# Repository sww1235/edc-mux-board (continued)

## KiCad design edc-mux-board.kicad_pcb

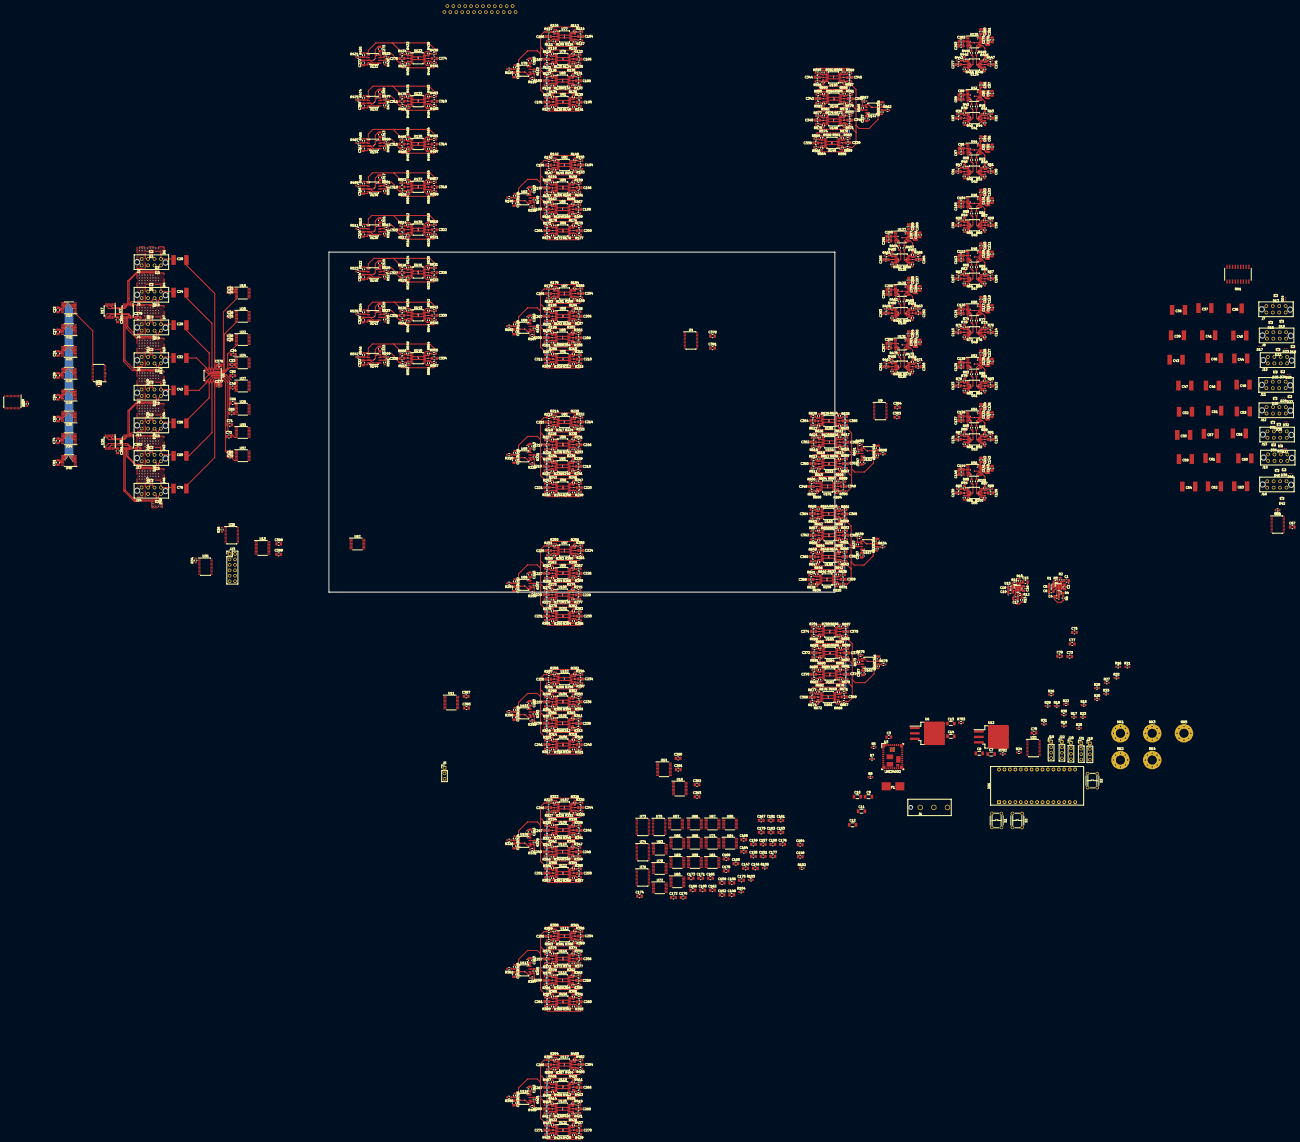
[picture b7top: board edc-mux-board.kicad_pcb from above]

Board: 4 copper layers, 1341 parts (1 on the bottom side), 1027 nets.

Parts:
C1, C4, C15, C17: 2u2F; C_0805_2012Metric_Pad1.15x1.50mm_HandSolder
C2, C16: 0.47uF; C_0805_2012Metric_Pad1.15x1.50mm_HandSolder
C3: 15uF; C_0805_2012Metric_Pad1.15x1.50mm_HandSolder
C5, C6, C18, C19: 4u7F; C_0805_2012Metric_Pad1.15x1.50mm_HandSolder
C7, C8, C13, C14: 10uF; C_1206_3216Metric_Pad1.24x1.80mm_HandSolder
C9, C10, C11, C12: 22uF; C_1206_3216Metric_Pad1.24x1.80mm_HandSolder
C20, C24, C28, C32, C35, C36, C37, C39, C40, C41, C42, C43, C44, C45, C46, C47, C48, C51, C52, C53, C55, C56, C57, C58, C59, C60, C61, C62, C63, C64, C69, C76: 1uF; Kemet_CAP_2220_5750Metric
C21, C22, C23, C25, C26, C27, C29, C30, C31, C33, C34, C38, C49, C50, C54, C65, C66, C67, C68, C70, C71, C72, C73, C74, C75, C77, C78, C79, C80, C81, C82, C83, C85, C86, C89, C90, C91, C93, C94, C97, C98, C99, C101, C102, C105, C106, C107, C109, C110, C113, C114, C115, C117, C118, C121, C122, C123, C125, C126, C129, C130, C131, C133, C134, C137, C138, C139, C141, C142, C145, C146, C147, C148, C149, C150, C151, C152, C153, C154, C155, C156, C157, C158, C159, C160, C161, C162, C163, C164, C165, C166, C167, C168, C169, C170, C171, C172, C173, C174, C175, C176, C177, C178, C179, C180, C181, C182, C183, C184, C185, C186, C187, C188, C189, C190, C191, C192, C193, C194, C195, C196, C197, C198, C199, C200, C201, C202, C203, C204, C205, C206, C207, C208, C209, C210, C211, C212, C213, C214, C215, C216, C217, C218, C219, C220, C221, C222, C223, C224, C225, C226, C227, C228, C229, C230, C231, C232, C233, C234, C235, C236, C237, C238, C239, C240, C241, C242, C243, C244, C245, C246, C247, C248, C249, C250, C251, C252, C253, C254, C255, C256, C257, C258, C259, C260, C261, C262, C263, C264, C265, C266, C267, C268, C269, C270, C271, C272, C273, C274, C275, C276, C277, C279, C280, C283, C284, C285, C287, C288, C291, C292, C293, C295, C296, C299, C300, C301, C303, C304, C307, C308, C309, C310, C311, C312, C313, C314, C315, C316, C317, C318, C319, C320, C321, C322, C323, C324, C325, C326, C327, C328, C329, C330, C331, C332, C333, C334, C335, C336, C337, C338, C339, C340, C341, C342, C343, C344, C345, C346, C347, C348, C349, C350, C351, C352, C353, C354, C355, C356, C357, C358, C359, C360, C361, C362, C363, C364, C365, C366, C367, C368, C369, C370, C371, C372, C373, C374, C375, C376, C377, C378, C379, C380, C381, C382, C383, C384, C385, C386, C387, C388, C389, C390, C391, C392, C393: 0.1uF; C_0805_2012Metric_Pad1.15x1.50mm_HandSolder
C84, C87, C88, C92, C95, C96, C100, C103, C104, C108, C111, C112, C116, C119, C120, C124, C127, C128, C132, C135, C136, C140, C143, C144, C278, C281, C282, C286, C289, C290, C294, C297, C298, C302, C305, C306: 0.01uF; C_0805_2012Metric_Pad1.15x1.50mm_HandSolder
D1, D4, D7, D10, D14, D17, D19, D23, D26, D29, D32, D34, D37, D41, D43, D46: TPD1E10B06; DPY_(R-PX1SON-N2)
D2, D3, D5, D6, D8, D9, D11, D12, D13, D15, D16, D18, D20, D21, D22, D24, D25, D27, D28, D30, D31, D33, D35, D36, D38, D39, D40, D42, D44, D45, D47, D48: 0582BQ; SC-75_3L
F1: 5A; NANO-0154-OMNI-BLOK-Fuse-Holder
J1: Power In; 43255-0121
J2: Device 0; 3-794681-8
J3: Device 1; 3-794681-8
J4: Device 2; 3-794681-8
J5: Mixer Audio In; PinHeader_1x03_P2.54mm_Vertical
J6: Device 3; 3-794681-8
J7: Headset 0; 3-794681-8
J8: Headset 1; 3-794681-8
J9: Device 4; 3-794681-8
J10: Headset 2; 3-794681-8
J11: Headset 3; 3-794681-8
J12: Headset 4; 3-794681-8
J13: Headset 5; 3-794681-8
J14: Device 5; 3-794681-8
J15: Headset 6; 3-794681-8
J16: Headset 7; 3-794681-8
J17: Device 6; 3-794681-8
J18: 5V-I2C-2; PinHeader_1x04_P2.54mm_Vertical
J19: 5V-I2C-3; PinHeader_1x04_P2.54mm_Vertical
J20: 5V-I2C-4; PinHeader_1x04_P2.54mm_Vertical
J21: 5V-I2C-5; PinHeader_1x04_P2.54mm_Vertical
J22: 5V-I2C-6; PinHeader_1x04_P2.54mm_Vertical
J23: Extra GPIO; PinHeader_2x06_P2.54mm_Vertical
J24: Device 7; 3-794681-8
J25: Outputs to Mixer; SDB-25PFFP-SR8001
MK1, MK2, MK3, MK4, MK5: Mounting_Hole_PAD; MountingHole_4.3mm_M4_Pad_Via
R2, R6: 75kΩ; R_0603_1608Metric_Pad0.84x1.00mm_HandSolder
R3, R4, R11, R12: 68kΩ; R_0603_1608Metric_Pad0.84x1.00mm_HandSolder
R5: 174kΩ; R_0603_1608Metric_Pad0.84x1.00mm_HandSolder
R7: 22.6kΩ; R_0603_1608Metric_Pad0.84x1.00mm_HandSolder
R8: 143kΩ; R_0603_1608Metric_Pad0.84x1.00mm_HandSolder
R10, R13: 220kΩ; R_0603_1608Metric_Pad0.84x1.00mm_HandSolder
R14, R24, R34, R35, R36, R37, R42, R45, R50, R53, R58, R61, R66, R69, R74, R77, R82, R85, R90, R93, R98, R101, R102, R103, R104, R105, R446, R449, R454, R457, R462, R465, R470, R473: 10kΩ; R_0603_1608Metric_Pad0.84x1.00mm_HandSolder
R15, R16, R17, R18, R19, R20, R21, R22, R23, R25, R26, R27, R28, R29, R30, R31, R32, R33: 4k7Ω; R_0603_1608Metric_Pad0.84x1.00mm_HandSolder
R38, R39, R40, R41, R43, R44, R46, R47, R48, R49, R51, R52, R54, R55, R56, R57, R59, R60, R62, R63, R64, R65, R67, R68, R70, R71, R72, R73, R75, R76, R78, R79, R80, R81, R83, R84, R86, R87, R88, R89, R91, R92, R94, R95, R96, R97, R99, R100, R106, R107, R108, R109, R110, R111, R112, R113, R114, R115, R116, R117, R118, R119, R120, R121, R122, R123, R124, R125, R126, R127, R128, R129, R130, R131, R132, R133, R134, R135, R136, R137, R138, R139, R140, R141, R142, R143, R144, R145, R146, R147, R148, R149, R150, R151, R152, R153, R154, R155, R156, R157, R158, R159, R160, R161, R162, R163, R164, R165, R166, R167, R168, R169, R170, R171, R172, R173, R174, R175, R176, R177, R178, R179, R180, R181, R182, R183, R184, R185, R186, R187, R188, R189, R190, R191, R192, R193, R194, R195, R196, R197, R198, R199, R200, R201, R202, R203, R204, R205, R206, R207, R208, R209, R210, R211, R212, R213, R214, R215, R216, R217, R218, R219, R220, R221, R222, R223, R224, R225, R226, R227, R228, R229, R230, R231, R232, R233, R234, R235, R236, R237, R238, R239, R240, R241, R242, R243, R244, R245, R246, R247, R248, R249, R250, R251, R252, R253, R254, R255, R256, R257, R258, R259, R260, R261, R262, R263, R264, R265, R266, R267, R268, R269, R270, R271, R272, R273, R274, R275, R276, R277, R278, R279, R280, R281, R282, R283, R284, R285, R286, R287, R288, R289, R290, R291, R292, R293, R294, R295, R296, R297, R298, R299, R300, R301, R302, R303, R304, R305, R306, R307, R308, R309, R310, R311, R312, R313, R314, R315, R316, R317, R318, R319, R320, R321, R322, R323, R324, R325, R326, R327, R328, R329, R330, R331, R332, R333, R334, R335, R336, R337, R338, R339, R340, R341, R342, R343, R344, R345, R346, R347, R348, R349, R350, R351, R352, R353, R354, R355, R356, R357, R358, R359, R360, R361, R362, R363, R364, R365, R366, R367, R368, R369, R370, R371, R372, R373, R374, R375, R376, R377, R378, R379, R380, R381, R382, R383, R384, R385, R386, R387, R388, R389, R390, R391, R392, R393, R394, R395, R396, R397, R398, R399, R400, R401, R402, R403, R404, R405, R406, R407, R408, R409, R410, R411, R412, R413, R414, R415, R416, R417, R418, R419, R420, R421, R422, R423, R424, R425, R426, R427, R428, R429, R430, R431, R432, R433, R434, R435, R436, R437, R438, R439, R440, R441, R442, R443, R444, R445, R447, R448, R450, R451, R452, R453, R455, R456, R458, R459, R460, R461, R463, R464, R466, R467, R468, R469, R471, R472, R474, R475, R476, R477, R478, R479, R480, R481, R482, R483, R484, R485, R486, R487, R488, R489, R490, R491, R492, R493, R494, R495, R496, R497, R498, R499, R500, R501, R502, R503, R504, R505, R506, R507, R508, R509, R510, R511, R512, R513, R514, R515, R516, R517, R518, R519, R520, R521, R522, R523, R524, R525, R526, R527, R528, R529, R530, R531, R532, R533, R534, R535, R536, R537, R538, R539, R540, R541, R542, R543, R544, R545, R546, R547, R548, R549, R550, R551, R552, R553, R554, R555, R556, R557, R558, R559, R560, R561, R562, R563, R564, R565, R566, R567, R568, R569, R570, R571, R572, R573, R574, R575, R576, R577, R578, R579, R580, R581, R582, R583, R584, R585, R586, R587, R588, R589, R590, R591, R592, R593, R594, R595, R596, R597, R598, R599, R600, R601, R602, R603, R604, R605, R606, R607, R608, R609, R610, R611, R612, R613, R614, R615, R616, R617, R618, R619, R620, R621, R622, R623, R624, R625, R626, R627, R628, R629, R630, R631, R632, R633, R634, R635, R636, R637, R638, R639, R640, R641, R642, R643, R644, R645, R646, R647, R648, R649, R650, R651, R652, R653, R654, R655, R656, R657, R658, R659, R660, R661, R662, R663, R664, R665, R666, R667, R668, R669, R670, R671, R672, R673, R674, R675, R676, R677, R678, R679, R680, R681, R682, R683, R684, R685, R686, R687, R688, R689, R690, R691, R692, R693, R694, R695, R696, R697, R698, R699, R700, R701: 100kΩ; R_0603_1608Metric_Pad0.84x1.00mm_HandSolder
R702, R703: 1.3Ω; R_0603_1608Metric_Pad0.84x1.00mm_HandSolder
RN1: 4818P-T02-202LF; SOM-18
S1: Nano Reset; TL1105
S2: I2C Reset; TL1105
S3: SPST Reset; TL1105
U1, U15: LM27762; WSON-12-1EP_3x2mm_P0.5mm
U2, U4, U9: ADG715; TSSOP-24_4.4x7.8mm_P0.65mm
U3: LMZ34002; RKG_(S-PB1QFN-N41)
U6: LM1085-12V; TO-263-3_TabPin4
U7, U8: TS12A44514; TSSOP-14_4.4x5mm_P0.65mm
U11, U13, U14, U16: ADG734; TSSOP-20_4.4x6.5mm_P0.65mm
U12: LM1085-5V; TO-263-3_TabPin4
U17, U26: 74ACT32; TSSOP-14_4.4x5mm_P0.65mm
U18, U19, U20, U21, U22, U23, U24, U25, U27, U28, U29, U30, U33, U34, U37, U40, U57, U58, U59, U60, U61, U62, U63, U64, U65, U66, U67, U68, U69, U70, U71, U72: ADG708; TSSOP-16_4.4x5mm_P0.65mm
U31, U35, U36, U38, U39, U73, U74, U75, U76: TCA9555; TSSOP-24_4.4x7.8mm_P0.65mm
U32: TCA9548A; TSSOP-24_4.4x7.8mm_P0.65mm
U41, U43, U45, U47, U49, U51, U53, U55, U77, U79, U80, U81, U82, U84, U85, U86, U87, U89, U90, U91, U92, U94, U95, U96, U97, U99, U100, U101, U102, U104, U105, U106, U107, U109, U110, U111, U112, U114, U115, U116, U117, U119, U120, U121, U123, U124, U126, U128, U130, U133, U135, U137, U139, U141, U143, U145, U146, U148, U149, U150, U151, U153, U154, U155, U156, U158, U159, U160, U161, U163, U164, U165: OPA1604; TSSOP-14_4.4x5mm_P0.65mm
U42, U44, U46, U48, U50, U52, U54, U56, U125, U127, U129, U131: DS1882; TSSOP-16_4.4x5mm_P0.65mm
U78, U83, U88, U93, U98, U103, U108, U113, U118, U122, U132, U134, U136, U138, U140, U142, U144, U147, U152, U157, U162: OPA1602; SOIC-8_3.9x4.9mm_P1.27mm
XA1: Nano_Headers; Nano-Header

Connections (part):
+2V5: C1.1, C21.1, C25.1, C29.1, C33.1, C49.1, C65.1, C71.1, C73.2, C77.2, C79.1, C146.1, C147.1, C150.1, C151.1, C154.1, C155.1, C158.1, C159.1, C162.1, C163.1, C166.1, C167.1, C170.1, C171.1, C174.1, C175.1, C178.2, C179.2, C180.2, C181.2, C376.2, C378.2, C383.2, C385.2, C388.2, C390.2, C392.2, J23.3, R2.1, R21.1, R22.1, R34.1, R36.1, R102.1, R103.1, R104.1, R105.1, U1.11, U2.2, U4.2, U4.24, U9.2, U9.22, U11.16, U13.16, U14.16, U16.16, U18.2, U18.13, U20.2, U20.13, U22.2, U22.13, U24.2, U24.13, U27.2, U27.13, U29.2, U29.13, U33.2, U33.13, U35.3, U35.24, U37.2, U37.13, U38.3, U38.21, U38.24, U57.2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
+3V3: C70.2, U32.24, XA1.17
+5V: C5.1, C14.1, C18.1, C23.1, C27.1, C31.1, C38.1, C54.1, C67.2, C68.1, C74.1, C75.2, C78.2, C81.1, C86.2, C87.2, C94.2, C95.2, C102.2, C103.2, C110.2, C111.2, C118.2, C119.2, C126.2, C127.2, C134.2, C135.2, C142.2, C143.2, C280.2, C281.2, C288.2, C289.2, C296.2, C297.2, C304.2, C305.2, C379.1, C380.1, C382.1, C386.1, J2.6, J3.6, J4.6, J6.6, J7.6, J8.6, J9.6, J10.6, J11.6, J12.6, J13.6, J14.6, J15.6, J16.6, J17.6, J18.1, J19.1, J20.1, J21.1, J22.1, J23.4, J24.6, R14.1, R15.1, R16.1, R17.1, R18.1, R19.1, R20.1, R23.1, R24.1, R25.1, R26.1, R27.1, R28.1, R29.1, R30.1, R31.1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
+5VA: C15.1, C84.2, C85.2, C92.2, C93.2, C100.2, C101.2, C108.2, C109.2, C116.2, C117.2, C124.2, C125.2, C132.2, C133.2, C140.2, C141.2, C278.2, C279.2, C286.2, C287.2, C294.2, C295.2, C302.2, C303.2, R10.1, U15.11, U42.15, U44.15, U46.15, U48.15, U50.15, U52.15, U54.15, U56.15, U125.15, U127.15, U129.15, U131.15
+12V: C3.1, C8.1, C13.1, C83.2, C91.2, C99.2, C107.2, C115.2, C123.2, C131.2, C139.2, C183.2, C185.2, C187.2, C189.2, C191.2, C193.2, C195.2, C197.2, C199.2, C201.2, C203.2, C205.2, C207.2, C209.2, C211.2, C213.2, C215.2, C217.2, C219.2, C221.2, C223.2, C225.2, C227.2, C229.2, C231.2, C233.2, C235.2, C237.2, C239.2, C241.2, C243.2, C245.2, C247.2, C249.2, C251.2, C253.2, C255.2, C257.2, C259.2, C261.2, C263.2, C265.2, C267.2, C269.2, C271.2, C273.2, C275.2, C277.2, C285.2, C293.2, C301.2, C309.2, C311.2, C313.2, C315.2, C317.2, C319.2, C321.2, C323.2, C325.2, C327.2, C329.2, C331.2, C333.2, C335.2, C337.2, C339.2, C341.2, C343.2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
-2.5V: C4.2, C22.2, C26.2, C30.2, C34.2, C50.2, C66.2, C72.2, C80.2, C148.2, C149.2, C152.2, C153.2, C156.2, C157.2, C160.2, C161.2, C164.2, C165.2, C168.2, C169.2, C172.2, C173.2, C176.2, C177.2, C377.1, C381.1, C384.1, C387.1, C389.1, C391.1, C393.1, R6.2, U1.6, U2.21, U4.21, U9.21, U11.5, U13.5, U14.5, U16.5, U18.3, U20.3, U22.3, U24.3, U27.3, U29.3, U33.3, U37.3, U57.3, U58.3, U59.3, U60.3, U61.3, U62.3, U63.3, U64.3, U65.3, U66.3, U67.3, U68.3, U69.3, U70.3, U71.3, U72.3
-5VA: C17.2, C88.2, C89.2, C96.2, C97.2, C104.2, C105.2, C112.2, C113.2, C120.2, C121.2, C128.2, C129.2, C136.2, C137.2, C144.2, C145.2, C282.2, C283.2, C290.2, C291.2, C298.2, C299.2, C306.2, C307.2, R13.2, U15.6, U42.4, U44.4, U46.4, U48.4, U50.4, U52.4, U54.4, U56.4, U125.4, U127.4, U129.4, U131.4
-12VA: C9.2, C10.2, C11.2, C12.2, C82.2, C90.2, C98.2, C106.2, C114.2, C122.2, C130.2, C138.2, C182.2, C184.2, C186.2, C188.2, C190.2, C192.2, C194.2, C196.2, C198.2, C200.2, C202.2, C204.2, C206.2, C208.2, C210.2, C212.2, C214.2, C216.2, C218.2, C220.2, C222.2, C224.2, C226.2, C228.2, C230.2, C232.2, C234.2, C236.2, C238.2, C240.2, C242.2, C244.2, C246.2, C248.2, C250.2, C252.2, C254.2, C256.2, C258.2, C260.2, C262.2, C264.2, C266.2, C268.2, C270.2, C272.2, C274.2, C276.2, C284.2, C292.2, C300.2, C308.2, C310.2, C312.2, C314.2, C316.2, C318.2, C320.2, C322.2, C324.2, C326.2, C328.2, C330.2, C332.2, C334.2, C336.2, C338.2, C340.2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
/Arduino Nano Header Connections + Ethernet connection/5V-SCL: R17.2, U32.22, XA1.24
/Arduino Nano Header Connections + Ethernet connection/5V-SDA: R18.2, U32.23, XA1.23
/Arduino Nano Header Connections + Ethernet connection/D2_SPST: S3.1, U2.23, U4.23, U9.23, XA1.5
/Arduino Nano Header Connections + Ethernet connection/D3_I2C: R24.2, S2.1, U32.3, XA1.6
/Arduino Nano Header Connections + Ethernet connection/D5_INT: R14.2, U31.1, XA1.8
/Arduino Nano Header Connections + Ethernet connection/Nano_RST: S1.1, XA1.3, XA1.28
/Audio Mux and Control/2v5-SCL-0: R21.2, U2.1, U4.1, U9.1, U32.8, U35.22, U38.22, U73.22, U74.22, U75.22, U76.22
/Audio Mux and Control/2v5-SDA-0: R22.2, U2.3, U4.3, U9.3, U32.9, U35.23, U38.23, U73.23, U74.23, U75.23, U76.23
/Audio Mux and Control/5V-SCL-0: R16.2, U31.22, U32.5, U36.22, U39.22, U42.14, U44.14, U46.14, U48.14, U50.14, U52.14, U54.14, U56.14
/Audio Mux and Control/5V-SCL-1: R20.2, U32.7, U125.14, U127.14, U129.14, U131.14
/Audio Mux and Control/5V-SCL-2: J18.2, J18.3, J19.2, J19.3, J20.2, J20.3, J21.2, J21.3, J22.2, J22.3, R23.2, R25.2, R26.2, R27.2, R28.2, R29.2, R30.2, R31.2, R32.2, R33.2, U32.10, U32.11, U32.13, U32.14, U32.15, U32.16, U32.17, U32.18, U32.19, U32.20
/Audio Mux and Control/5V-SDA-0: R15.2, U31.23, U32.4, U36.23, U39.23, U42.13, U44.13, U46.13, U48.13, U50.13, U52.13, U54.13, U56.13
/Audio Mux and Control/5V-SDA-1: R19.2, U32.6, U125.13, U127.13, U129.13, U131.13
/Audio Mux and Control/AMP-MIC-IN-0-0: R558.1, U18.4, U146.1
/Audio Mux and Control/AMP-MIC-IN-0-1: R564.1, U20.4, U146.14
/Audio Mux and Control/AMP-MIC-IN-0-2: R570.1, U22.4, U148.1
/Audio Mux and Control/AMP-MIC-IN-0-3: R574.1, U24.4, U148.14
/Audio Mux and Control/AMP-MIC-IN-0-4: R578.1, U27.4, U149.1
/Audio Mux and Control/AMP-MIC-IN-0-5: R582.1, U29.4, U149.14
/Audio Mux and Control/AMP-MIC-IN-0-6: R586.1, U33.4, U150.1
/Audio Mux and Control/AMP-MIC-IN-0-7: R590.1, U37.4, U150.14
/Audio Mux and Control/AMP-MIC-IN-1-0: R561.1, U18.5, U146.7
/Audio Mux and Control/AMP-MIC-IN-1-1: R568.1, U20.5, U146.8
/Audio Mux and Control/AMP-MIC-IN-1-2: R572.1, U22.5, U148.7
/Audio Mux and Control/AMP-MIC-IN-1-3: R576.1, U24.5, U148.8
/Audio Mux and Control/AMP-MIC-IN-1-4: R580.1, U27.5, U149.7
/Audio Mux and Control/AMP-MIC-IN-1-5: R584.1, U29.5, U149.8
/Audio Mux and Control/AMP-MIC-IN-1-6: R588.1, U33.5, U150.7
/Audio Mux and Control/AMP-MIC-IN-1-7: R592.1, U37.5, U150.8
/Audio Mux and Control/AMP-MIC-IN-2-0: R594.1, U18.6, U151.1
/Audio Mux and Control/AMP-MIC-IN-2-1: R600.1, U20.6, U151.14
/Audio Mux and Control/AMP-MIC-IN-2-2: R606.1, U22.6, U153.1
/Audio Mux and Control/AMP-MIC-IN-2-3: R610.1, U24.6, U153.14
/Audio Mux and Control/AMP-MIC-IN-2-4: R614.1, U27.6, U154.1
/Audio Mux and Control/AMP-MIC-IN-2-5: R618.1, U29.6, U154.14
/Audio Mux and Control/AMP-MIC-IN-2-6: R622.1, U33.6, U155.1
/Audio Mux and Control/AMP-MIC-IN-2-7: R626.1, U37.6, U155.14
/Audio Mux and Control/AMP-MIC-IN-3-0: R597.1, U18.7, U151.7
/Audio Mux and Control/AMP-MIC-IN-3-1: R604.1, U20.7, U151.8
/Audio Mux and Control/AMP-MIC-IN-3-2: R608.1, U22.7, U153.7
/Audio Mux and Control/AMP-MIC-IN-3-3: R612.1, U24.7, U153.8
/Audio Mux and Control/AMP-MIC-IN-3-4: R616.1, U27.7, U154.7
/Audio Mux and Control/AMP-MIC-IN-3-5: R620.1, U29.7, U154.8
/Audio Mux and Control/AMP-MIC-IN-3-6: R624.1, U33.7, U155.7
/Audio Mux and Control/AMP-MIC-IN-3-7: R628.1, U37.7, U155.8
/Audio Mux and Control/AMP-MIC-IN-4-0: R630.1, U18.12, U156.1
/Audio Mux and Control/AMP-MIC-IN-4-1: R636.1, U20.12, U156.14
/Audio Mux and Control/AMP-MIC-IN-4-2: R642.1, U22.12, U158.1
/Audio Mux and Control/AMP-MIC-IN-4-3: R646.1, U24.12, U158.14
/Audio Mux and Control/AMP-MIC-IN-4-4: R650.1, U27.12, U159.1
/Audio Mux and Control/AMP-MIC-IN-4-5: R654.1, U29.12, U159.14
/Audio Mux and Control/AMP-MIC-IN-4-6: R658.1, U33.12, U160.1
/Audio Mux and Control/AMP-MIC-IN-4-7: R662.1, U37.12, U160.14
/Audio Mux and Control/AMP-MIC-IN-5-0: R633.1, U18.11, U156.7
/Audio Mux and Control/AMP-MIC-IN-5-1: R640.1, U20.11, U156.8
/Audio Mux and Control/AMP-MIC-IN-5-2: R644.1, U22.11, U158.7
/Audio Mux and Control/AMP-MIC-IN-5-3: R648.1, U24.11, U158.8
/Audio Mux and Control/AMP-MIC-IN-5-4: R652.1, U27.11, U159.7
/Audio Mux and Control/AMP-MIC-IN-5-5: R656.1, U29.11, U159.8
/Audio Mux and Control/AMP-MIC-IN-5-6: R660.1, U33.11, U160.7
/Audio Mux and Control/AMP-MIC-IN-5-7: R664.1, U37.11, U160.8
/Audio Mux and Control/AMP-MIC-IN-6-0: R666.1, U18.10, U161.1
/Audio Mux and Control/AMP-MIC-IN-6-1: R672.1, U20.10, U161.14
/Audio Mux and Control/AMP-MIC-IN-6-2: R678.1, U22.10, U163.1
/Audio Mux and Control/AMP-MIC-IN-6-3: R682.1, U24.10, U163.14
/Audio Mux and Control/AMP-MIC-IN-6-4: R686.1, U27.10, U164.1
/Audio Mux and Control/AMP-MIC-IN-6-5: R690.1, U29.10, U164.14
/Audio Mux and Control/AMP-MIC-IN-6-6: R694.1, U33.10, U165.1
/Audio Mux and Control/AMP-MIC-IN-6-7: R698.1, U37.10, U165.14
/Audio Mux and Control/AMP-MIC-IN-7-0: R669.1, U18.9, U161.7
/Audio Mux and Control/AMP-MIC-IN-7-1: R676.1, U20.9, U161.8
/Audio Mux and Control/AMP-MIC-IN-7-2: R680.1, U22.9, U163.7
/Audio Mux and Control/AMP-MIC-IN-7-3: R684.1, U24.9, U163.8
/Audio Mux and Control/AMP-MIC-IN-7-4: R688.1, U27.9, U164.7
/Audio Mux and Control/AMP-MIC-IN-7-5: R692.1, U29.9, U164.8
/Audio Mux and Control/AMP-MIC-IN-7-6: R696.1, U33.9, U165.7
/Audio Mux and Control/AMP-MIC-IN-7-7: R700.1, U37.9, U165.8
/Audio Mux and Control/DEV-MIC-IN-XBAR-CTL0: U18.1, U35.13
/Audio Mux and Control/DEV-MIC-IN-XBAR-CTL1: U18.16, U35.14
/Audio Mux and Control/DEV-MIC-IN-XBAR-CTL2: U18.15, U35.15
/Audio Mux and Control/DEV-MIC-IN-XBAR-CTL3: U20.1, U35.16
/Audio Mux and Control/DEV-MIC-IN-XBAR-CTL4: U20.16, U35.17
/Audio Mux and Control/DEV-MIC-IN-XBAR-CTL5: U20.15, U35.18
/Audio Mux and Control/DEV-MIC-IN-XBAR-CTL6: U22.1, U35.19
/Audio Mux and Control/DEV-MIC-IN-XBAR-CTL7: U22.16, U35.20
/Audio Mux and Control/DEV-MIC-IN-XBAR-CTL8: U22.15, U38.4
/Audio Mux and Control/DEV-MIC-IN-XBAR-CTL9: U24.1, U38.5
/Audio Mux and Control/DEV-MIC-IN-XBAR-CTL10: U24.16, U38.6
/Audio Mux and Control/DEV-MIC-IN-XBAR-CTL11: U24.15, U38.7
/Audio Mux and Control/DEV-MIC-IN-XBAR-CTL12: U27.1, U38.8
/Audio Mux and Control/DEV-MIC-IN-XBAR-CTL13: U27.16, U38.9
/Audio Mux and Control/DEV-MIC-IN-XBAR-CTL14: U27.15, U38.10
/Audio Mux and Control/DEV-MIC-IN-XBAR-CTL15: U29.1, U38.11
/Audio Mux and Control/DEV-MIC-IN-XBAR-CTL16: U29.16, U38.13
/Audio Mux and Control/DEV-MIC-IN-XBAR-CTL17: U29.15, U38.14
/Audio Mux and Control/DEV-MIC-IN-XBAR-CTL18: U33.1, U38.15
/Audio Mux and Control/DEV-MIC-IN-XBAR-CTL19: U33.16, U38.16
/Audio Mux and Control/DEV-MIC-IN-XBAR-CTL20: U33.15, U38.17
/Audio Mux and Control/DEV-MIC-IN-XBAR-CTL21: U37.1, U38.18
/Audio Mux and Control/DEV-MIC-IN-XBAR-CTL22: U37.16, U38.19
/Audio Mux and Control/DEV-MIC-IN-XBAR-CTL23: U37.15, U38.20
/Audio Mux and Control/DEV-PTT-XBAR-CTL0: U19.1, U36.13
/Audio Mux and Control/DEV-PTT-XBAR-CTL1: U19.16, U36.14
/Audio Mux and Control/DEV-PTT-XBAR-CTL2: U19.15, U36.15
/Audio Mux and Control/DEV-PTT-XBAR-CTL3: U21.1, U36.16
/Audio Mux and Control/DEV-PTT-XBAR-CTL4: U21.16, U36.17
/Audio Mux and Control/DEV-PTT-XBAR-CTL5: U21.15, U36.18
/Audio Mux and Control/DEV-PTT-XBAR-CTL6: U23.1, U36.19
/Audio Mux and Control/DEV-PTT-XBAR-CTL7: U23.16, U36.20
/Audio Mux and Control/DEV-PTT-XBAR-CTL8: U23.15, U39.4
/Audio Mux and Control/DEV-PTT-XBAR-CTL9: U25.1, U39.5
/Audio Mux and Control/DEV-PTT-XBAR-CTL10: U25.16, U39.6
/Audio Mux and Control/DEV-PTT-XBAR-CTL11: U25.15, U39.7
/Audio Mux and Control/DEV-PTT-XBAR-CTL12: U28.1, U39.8
/Audio Mux and Control/DEV-PTT-XBAR-CTL13: U28.16, U39.9
/Audio Mux and Control/DEV-PTT-XBAR-CTL14: U28.15, U39.10
/Audio Mux and Control/DEV-PTT-XBAR-CTL15: U30.1, U39.11
/Audio Mux and Control/DEV-PTT-XBAR-CTL16: U30.16, U39.13
/Audio Mux and Control/DEV-PTT-XBAR-CTL17: U30.15, U39.14
/Audio Mux and Control/DEV-PTT-XBAR-CTL18: U34.1, U39.15
/Audio Mux and Control/DEV-PTT-XBAR-CTL19: U34.16, U39.16
/Audio Mux and Control/DEV-PTT-XBAR-CTL20: U34.15, U39.17
/Audio Mux and Control/DEV-PTT-XBAR-CTL21: U39.18, U40.1
/Audio Mux and Control/DEV-PTT-XBAR-CTL22: U39.19, U40.16
/Audio Mux and Control/DEV-PTT-XBAR-CTL23: U39.20, U40.15
/Audio Mux and Control/Device LR Distro Amplifier 0/L_IN: D2.1, J2.2, R431.2
/Audio Mux and Control/Device LR Distro Amplifier 0/R_IN: D2.2, J2.3, R435.2
/Audio Mux and Control/Device LR Distro Amplifier 1/L_IN: D5.1, J3.2, R475.2
/Audio Mux and Control/Device LR Distro Amplifier 1/R_IN: D5.2, J3.3, R479.2
/Audio Mux and Control/Device LR Distro Amplifier 2/L_IN: D8.1, J4.2, R487.2
/Audio Mux and Control/Device LR Distro Amplifier 2/R_IN: D8.2, J4.3, R491.2
/Audio Mux and Control/Device LR Distro Amplifier 3/L_IN: D11.1, J6.2, R499.2
/Audio Mux and Control/Device LR Distro Amplifier 3/R_IN: D11.2, J6.3, R503.2
/Audio Mux and Control/Device LR Distro Amplifier 4/L_IN: D20.1, J9.2, R511.2
/Audio Mux and Control/Device LR Distro Amplifier 4/R_IN: D20.2, J9.3, R515.2
/Audio Mux and Control/Device LR Distro Amplifier 5/L_IN: D35.1, J14.2, R523.2
/Audio Mux and Control/Device LR Distro Amplifier 5/R_IN: D35.2, J14.3, R527.2
/Audio Mux and Control/Device LR Distro Amplifier 6/L_IN: D44.1, J17.2, R535.2
/Audio Mux and Control/Device LR Distro Amplifier 6/R_IN: D44.2, J17.3, R539.2
/Audio Mux and Control/Device LR Distro Amplifier 7/L_IN: D47.1, J24.2, R547.2
/Audio Mux and Control/Device LR Distro Amplifier 7/R_IN: D47.2, J24.3, R551.2
/Audio Mux and Control/Dual Mic Distro Amp 0/L_Distro_Bus: R559.2, R560.1, R566.2, R571.2, R575.2, R579.2, R583.2, R587.2, R591.2, U147.1
/Audio Mux and Control/Dual Mic Distro Amp 0/L_IN: R444.1, R562.2, U124.7
/Audio Mux and Control/Dual Mic Distro Amp 0/R_Distro_Bus: R563.2, R565.1, R569.2, R573.2, R577.2, R581.2, R585.2, R589.2, R593.2, U147.7
/Audio Mux and Control/Dual Mic Distro Amp 0/R_IN: R448.1, R567.2, U124.8
/Audio Mux and Control/Dual Mic Distro Amp 1/L_Distro_Bus: R595.2, R596.1, R602.2, R607.2, R611.2, R615.2, R619.2, R623.2, R627.2, U152.1
/Audio Mux and Control/Dual Mic Distro Amp 1/L_IN: R452.1, R598.2, U126.7
/Audio Mux and Control/Dual Mic Distro Amp 1/R_Distro_Bus: R599.2, R601.1, R605.2, R609.2, R613.2, R617.2, R621.2, R625.2, R629.2, U152.7
/Audio Mux and Control/Dual Mic Distro Amp 1/R_IN: R456.1, R603.2, U126.8
/Audio Mux and Control/Dual Mic Distro Amp 2/L_Distro_Bus: R631.2, R632.1, R638.2, R643.2, R647.2, R651.2, R655.2, R659.2, R663.2, U157.1
/Audio Mux and Control/Dual Mic Distro Amp 2/L_IN: R460.1, R634.2, U128.7
/Audio Mux and Control/Dual Mic Distro Amp 2/R_Distro_Bus: R635.2, R637.1, R641.2, R645.2, R649.2, R653.2, R657.2, R661.2, R665.2, U157.7
/Audio Mux and Control/Dual Mic Distro Amp 2/R_IN: R464.1, R639.2, U128.8
/Audio Mux and Control/Dual Mic Distro Amp 3/L_Distro_Bus: R667.2, R668.1, R674.2, R679.2, R683.2, R687.2, R691.2, R695.2, R699.2, U162.1
/Audio Mux and Control/Dual Mic Distro Amp 3/L_IN: R468.1, R670.2, U130.7
/Audio Mux and Control/Dual Mic Distro Amp 3/R_Distro_Bus: R671.2, R673.1, R677.2, R681.2, R685.2, R689.2, R693.2, R697.2, R701.2, U162.7
/Audio Mux and Control/Dual Mic Distro Amp 3/R_IN: R472.1, R675.2, U130.8
/Audio Mux and Control/HEADSET-AUDIO-SOURCE-L-0: R110.2, R438.1, U123.14
/Audio Mux and Control/HEADSET-AUDIO-SOURCE-L-1: R146.2, R482.1, U133.14
/Audio Mux and Control/HEADSET-AUDIO-SOURCE-L-2: R182.2, R494.1, U135.14
/Audio Mux and Control/HEADSET-AUDIO-SOURCE-L-3: R218.2, R506.1, U137.14
/Audio Mux and Control/HEADSET-AUDIO-SOURCE-L-4: R362.2, R518.1, U139.14
/Audio Mux and Control/HEADSET-AUDIO-SOURCE-L-5: R254.2, R530.1, U141.14
/Audio Mux and Control/HEADSET-AUDIO-SOURCE-L-6: R290.2, R542.1, U143.14
/Audio Mux and Control/HEADSET-AUDIO-SOURCE-L-7: R326.2, R554.1, U145.14
/Audio Mux and Control/HEADSET-AUDIO-SOURCE-R-0: R115.2, R440.1, U123.8
/Audio Mux and Control/HEADSET-AUDIO-SOURCE-R-1: R151.2, R484.1, U133.8
/Audio Mux and Control/HEADSET-AUDIO-SOURCE-R-2: R187.2, R496.1, U135.8
/Audio Mux and Control/HEADSET-AUDIO-SOURCE-R-3: R223.2, R508.1, U137.8
/Audio Mux and Control/HEADSET-AUDIO-SOURCE-R-4: R367.2, R520.1, U139.8
/Audio Mux and Control/HEADSET-AUDIO-SOURCE-R-5: R259.2, R532.1, U141.8
/Audio Mux and Control/HEADSET-AUDIO-SOURCE-R-6: R295.2, R544.1, U143.8
/Audio Mux and Control/HEADSET-AUDIO-SOURCE-R-7: R331.2, R556.1, U145.8
/Audio Mux and Control/Headset LR audio out Mux and Source Selection/DEV0_L_0: R106.1, U57.4, U77.1
/Audio Mux and Control/Headset LR audio out Mux and Source Selection/DEV0_L_1: R112.1, U59.4, U77.14
/Audio Mux and Control/Headset LR audio out Mux and Source Selection/DEV0_L_2: R118.1, U61.4, U79.1
/Audio Mux and Control/Headset LR audio out Mux and Source Selection/DEV0_L_3: R122.1, U63.4, U79.14
/Audio Mux and Control/Headset LR audio out Mux and Source Selection/DEV0_L_4: R126.1, U65.4, U80.1
/Audio Mux and Control/Headset LR audio out Mux and Source Selection/DEV0_L_5: R130.1, U67.4, U80.14
/Audio Mux and Control/Headset LR audio out Mux and Source Selection/DEV0_L_6: R134.1, U69.4, U81.1
/Audio Mux and Control/Headset LR audio out Mux and Source Selection/DEV0_L_7: R138.1, U71.4, U81.14
/Audio Mux and Control/Headset LR audio out Mux and Source Selection/DEV0_R_0: R109.1, U58.4, U77.7
/Audio Mux and Control/Headset LR audio out Mux and Source Selection/DEV0_R_1: R116.1, U60.4, U77.8
/Audio Mux and Control/Headset LR audio out Mux and Source Selection/DEV0_R_2: R120.1, U62.4, U79.7
/Audio Mux and Control/Headset LR audio out Mux and Source Selection/DEV0_R_3: R124.1, U64.4, U79.8
/Audio Mux and Control/Headset LR audio out Mux and Source Selection/DEV0_R_4: R128.1, U66.4, U80.7
/Audio Mux and Control/Headset LR audio out Mux and Source Selection/DEV0_R_5: R132.1, U68.4, U80.8
/Audio Mux and Control/Headset LR audio out Mux and Source Selection/DEV0_R_6: R136.1, U70.4, U81.7
/Audio Mux and Control/Headset LR audio out Mux and Source Selection/DEV0_R_7: R140.1, U72.4, U81.8
/Audio Mux and Control/Headset LR audio out Mux and Source Selection/DEV1_L_0: R142.1, U57.5, U82.1
/Audio Mux and Control/Headset LR audio out Mux and Source Selection/DEV1_L_1: R148.1, U59.5, U82.14
/Audio Mux and Control/Headset LR audio out Mux and Source Selection/DEV1_L_2: R154.1, U61.5, U84.1
/Audio Mux and Control/Headset LR audio out Mux and Source Selection/DEV1_L_3: R158.1, U63.5, U84.14
/Audio Mux and Control/Headset LR audio out Mux and Source Selection/DEV1_L_4: R162.1, U65.5, U85.1
/Audio Mux and Control/Headset LR audio out Mux and Source Selection/DEV1_L_5: R166.1, U67.5, U85.14
/Audio Mux and Control/Headset LR audio out Mux and Source Selection/DEV1_L_6: R170.1, U69.5, U86.1
/Audio Mux and Control/Headset LR audio out Mux and Source Selection/DEV1_L_7: R174.1, U71.5, U86.14
/Audio Mux and Control/Headset LR audio out Mux and Source Selection/DEV1_R_0: R145.1, U58.5, U82.7
/Audio Mux and Control/Headset LR audio out Mux and Source Selection/DEV1_R_1: R152.1, U60.5, U82.8
/Audio Mux and Control/Headset LR audio out Mux and Source Selection/DEV1_R_2: R156.1, U62.5, U84.7
/Audio Mux and Control/Headset LR audio out Mux and Source Selection/DEV1_R_3: R160.1, U64.5, U84.8
/Audio Mux and Control/Headset LR audio out Mux and Source Selection/DEV1_R_4: R164.1, U66.5, U85.7
/Audio Mux and Control/Headset LR audio out Mux and Source Selection/DEV1_R_5: R168.1, U68.5, U85.8
/Audio Mux and Control/Headset LR audio out Mux and Source Selection/DEV1_R_6: R172.1, U70.5, U86.7
/Audio Mux and Control/Headset LR audio out Mux and Source Selection/DEV1_R_7: R176.1, U72.5, U86.8
/Audio Mux and Control/Headset LR audio out Mux and Source Selection/DEV2_L_0: R178.1, U57.6, U87.1
/Audio Mux and Control/Headset LR audio out Mux and Source Selection/DEV2_L_1: R184.1, U59.6, U87.14
/Audio Mux and Control/Headset LR audio out Mux and Source Selection/DEV2_L_2: R190.1, U61.6, U89.1
/Audio Mux and Control/Headset LR audio out Mux and Source Selection/DEV2_L_3: R194.1, U63.6, U89.14
/Audio Mux and Control/Headset LR audio out Mux and Source Selection/DEV2_L_4: R198.1, U65.6, U90.1
/Audio Mux and Control/Headset LR audio out Mux and Source Selection/DEV2_L_5: R202.1, U67.6, U90.14
/Audio Mux and Control/Headset LR audio out Mux and Source Selection/DEV2_L_6: R206.1, U69.6, U91.1
/Audio Mux and Control/Headset LR audio out Mux and Source Selection/DEV2_L_7: R210.1, U71.6, U91.14
/Audio Mux and Control/Headset LR audio out Mux and Source Selection/DEV2_R_0: R181.1, U58.6, U87.7
/Audio Mux and Control/Headset LR audio out Mux and Source Selection/DEV2_R_1: R188.1, U60.6, U87.8
/Audio Mux and Control/Headset LR audio out Mux and Source Selection/DEV2_R_2: R192.1, U62.6, U89.7
/Audio Mux and Control/Headset LR audio out Mux and Source Selection/DEV2_R_3: R196.1, U64.6, U89.8
/Audio Mux and Control/Headset LR audio out Mux and Source Selection/DEV2_R_4: R200.1, U66.6, U90.7
/Audio Mux and Control/Headset LR audio out Mux and Source Selection/DEV2_R_5: R204.1, U68.6, U90.8
/Audio Mux and Control/Headset LR audio out Mux and Source Selection/DEV2_R_6: R208.1, U70.6, U91.7
/Audio Mux and Control/Headset LR audio out Mux and Source Selection/DEV2_R_7: R212.1, U72.6, U91.8
/Audio Mux and Control/Headset LR audio out Mux and Source Selection/DEV3_L_0: R214.1, U57.7, U92.1
/Audio Mux and Control/Headset LR audio out Mux and Source Selection/DEV3_L_1: R220.1, U59.7, U92.14
/Audio Mux and Control/Headset LR audio out Mux and Source Selection/DEV3_L_2: R226.1, U61.7, U94.1
/Audio Mux and Control/Headset LR audio out Mux and Source Selection/DEV3_L_3: R230.1, U63.7, U94.14
/Audio Mux and Control/Headset LR audio out Mux and Source Selection/DEV3_L_4: R234.1, U65.7, U95.1
/Audio Mux and Control/Headset LR audio out Mux and Source Selection/DEV3_L_5: R238.1, U67.7, U95.14
/Audio Mux and Control/Headset LR audio out Mux and Source Selection/DEV3_L_6: R242.1, U69.7, U96.1
/Audio Mux and Control/Headset LR audio out Mux and Source Selection/DEV3_L_7: R246.1, U71.7, U96.14
/Audio Mux and Control/Headset LR audio out Mux and Source Selection/DEV3_R_0: R217.1, U58.7, U92.7
/Audio Mux and Control/Headset LR audio out Mux and Source Selection/DEV3_R_1: R224.1, U60.7, U92.8
/Audio Mux and Control/Headset LR audio out Mux and Source Selection/DEV3_R_2: R228.1, U62.7, U94.7
/Audio Mux and Control/Headset LR audio out Mux and Source Selection/DEV3_R_3: R232.1, U64.7, U94.8
/Audio Mux and Control/Headset LR audio out Mux and Source Selection/DEV3_R_4: R236.1, U66.7, U95.7
/Audio Mux and Control/Headset LR audio out Mux and Source Selection/DEV3_R_5: R240.1, U68.7, U95.8
/Audio Mux and Control/Headset LR audio out Mux and Source Selection/DEV3_R_6: R244.1, U70.7, U96.7
/Audio Mux and Control/Headset LR audio out Mux and Source Selection/DEV3_R_7: R248.1, U72.7, U96.8
/Audio Mux and Control/Headset LR audio out Mux and Source Selection/DEV4_L_0: R358.1, U57.12, U112.1
/Audio Mux and Control/Headset LR audio out Mux and Source Selection/DEV4_L_1: R364.1, U59.12, U112.14
/Audio Mux and Control/Headset LR audio out Mux and Source Selection/DEV4_L_2: R370.1, U61.12, U114.1
/Audio Mux and Control/Headset LR audio out Mux and Source Selection/DEV4_L_3: R374.1, U63.12, U114.14
/Audio Mux and Control/Headset LR audio out Mux and Source Selection/DEV4_L_4: R378.1, U65.12, U115.1
/Audio Mux and Control/Headset LR audio out Mux and Source Selection/DEV4_L_5: R382.1, U67.12, U115.14
/Audio Mux and Control/Headset LR audio out Mux and Source Selection/DEV4_L_6: R386.1, U69.12, U116.1
/Audio Mux and Control/Headset LR audio out Mux and Source Selection/DEV4_L_7: R390.1, U71.12, U116.14
/Audio Mux and Control/Headset LR audio out Mux and Source Selection/DEV4_R_0: R361.1, U58.12, U112.7
/Audio Mux and Control/Headset LR audio out Mux and Source Selection/DEV4_R_1: R368.1, U60.12, U112.8
/Audio Mux and Control/Headset LR audio out Mux and Source Selection/DEV4_R_2: R372.1, U62.12, U114.7
/Audio Mux and Control/Headset LR audio out Mux and Source Selection/DEV4_R_3: R376.1, U64.12, U114.8
/Audio Mux and Control/Headset LR audio out Mux and Source Selection/DEV4_R_4: R380.1, U66.12, U115.7
/Audio Mux and Control/Headset LR audio out Mux and Source Selection/DEV4_R_5: R384.1, U68.12, U115.8
/Audio Mux and Control/Headset LR audio out Mux and Source Selection/DEV4_R_6: R388.1, U70.12, U116.7
/Audio Mux and Control/Headset LR audio out Mux and Source Selection/DEV4_R_7: R392.1, U72.12, U116.8
/Audio Mux and Control/Headset LR audio out Mux and Source Selection/DEV5_L_0: R250.1, U57.11, U97.1
/Audio Mux and Control/Headset LR audio out Mux and Source Selection/DEV5_L_1: R256.1, U59.11, U97.14
/Audio Mux and Control/Headset LR audio out Mux and Source Selection/DEV5_L_2: R262.1, U61.11, U99.1
/Audio Mux and Control/Headset LR audio out Mux and Source Selection/DEV5_L_3: R266.1, U63.11, U99.14
/Audio Mux and Control/Headset LR audio out Mux and Source Selection/DEV5_L_4: R270.1, U65.11, U100.1
/Audio Mux and Control/Headset LR audio out Mux and Source Selection/DEV5_L_5: R274.1, U67.11, U100.14
/Audio Mux and Control/Headset LR audio out Mux and Source Selection/DEV5_L_6: R278.1, U69.11, U101.1
/Audio Mux and Control/Headset LR audio out Mux and Source Selection/DEV5_L_7: R282.1, U71.11, U101.14
/Audio Mux and Control/Headset LR audio out Mux and Source Selection/DEV5_R_0: R253.1, U58.11, U97.7
/Audio Mux and Control/Headset LR audio out Mux and Source Selection/DEV5_R_1: R260.1, U60.11, U97.8
/Audio Mux and Control/Headset LR audio out Mux and Source Selection/DEV5_R_2: R264.1, U62.11, U99.7
/Audio Mux and Control/Headset LR audio out Mux and Source Selection/DEV5_R_3: R268.1, U64.11, U99.8
/Audio Mux and Control/Headset LR audio out Mux and Source Selection/DEV5_R_4: R272.1, U66.11, U100.7
/Audio Mux and Control/Headset LR audio out Mux and Source Selection/DEV5_R_5: R276.1, U68.11, U100.8
/Audio Mux and Control/Headset LR audio out Mux and Source Selection/DEV5_R_6: R280.1, U70.11, U101.7
/Audio Mux and Control/Headset LR audio out Mux and Source Selection/DEV5_R_7: R284.1, U72.11, U101.8
/Audio Mux and Control/Headset LR audio out Mux and Source Selection/DEV6_L_0: R286.1, U57.10, U102.1
/Audio Mux and Control/Headset LR audio out Mux and Source Selection/DEV6_L_1: R292.1, U59.10, U102.14
/Audio Mux and Control/Headset LR audio out Mux and Source Selection/DEV6_L_2: R298.1, U61.10, U104.1
/Audio Mux and Control/Headset LR audio out Mux and Source Selection/DEV6_L_3: R302.1, U63.10, U104.14
/Audio Mux and Control/Headset LR audio out Mux and Source Selection/DEV6_L_4: R306.1, U65.10, U105.1
/Audio Mux and Control/Headset LR audio out Mux and Source Selection/DEV6_L_5: R310.1, U67.10, U105.14
/Audio Mux and Control/Headset LR audio out Mux and Source Selection/DEV6_L_6: R314.1, U69.10, U106.1
/Audio Mux and Control/Headset LR audio out Mux and Source Selection/DEV6_L_7: R318.1, U71.10, U106.14
/Audio Mux and Control/Headset LR audio out Mux and Source Selection/DEV6_R_0: R289.1, U58.10, U102.7
/Audio Mux and Control/Headset LR audio out Mux and Source Selection/DEV6_R_1: R296.1, U60.10, U102.8
/Audio Mux and Control/Headset LR audio out Mux and Source Selection/DEV6_R_2: R300.1, U62.10, U104.7
/Audio Mux and Control/Headset LR audio out Mux and Source Selection/DEV6_R_3: R304.1, U64.10, U104.8
/Audio Mux and Control/Headset LR audio out Mux and Source Selection/DEV6_R_4: R308.1, U66.10, U105.7
/Audio Mux and Control/Headset LR audio out Mux and Source Selection/DEV6_R_5: R312.1, U68.10, U105.8
/Audio Mux and Control/Headset LR audio out Mux and Source Selection/DEV6_R_6: R316.1, U70.10, U106.7
/Audio Mux and Control/Headset LR audio out Mux and Source Selection/DEV6_R_7: R320.1, U72.10, U106.8
/Audio Mux and Control/Headset LR audio out Mux and Source Selection/DEV7_L_0: R322.1, U57.9, U107.1
/Audio Mux and Control/Headset LR audio out Mux and Source Selection/DEV7_L_1: R328.1, U59.9, U107.14
/Audio Mux and Control/Headset LR audio out Mux and Source Selection/DEV7_L_2: R334.1, U61.9, U109.1
/Audio Mux and Control/Headset LR audio out Mux and Source Selection/DEV7_L_3: R338.1, U63.9, U109.14
/Audio Mux and Control/Headset LR audio out Mux and Source Selection/DEV7_L_4: R342.1, U65.9, U110.1
/Audio Mux and Control/Headset LR audio out Mux and Source Selection/DEV7_L_5: R346.1, U67.9, U110.14
/Audio Mux and Control/Headset LR audio out Mux and Source Selection/DEV7_L_6: R350.1, U69.9, U111.1
/Audio Mux and Control/Headset LR audio out Mux and Source Selection/DEV7_L_7: R354.1, U71.9, U111.14
/Audio Mux and Control/Headset LR audio out Mux and Source Selection/DEV7_R_0: R325.1, U58.9, U107.7
/Audio Mux and Control/Headset LR audio out Mux and Source Selection/DEV7_R_1: R332.1, U60.9, U107.8
/Audio Mux and Control/Headset LR audio out Mux and Source Selection/DEV7_R_2: R336.1, U62.9, U109.7
/Audio Mux and Control/Headset LR audio out Mux and Source Selection/DEV7_R_3: R340.1, U64.9, U109.8
/Audio Mux and Control/Headset LR audio out Mux and Source Selection/DEV7_R_4: R344.1, U66.9, U110.7
/Audio Mux and Control/Headset LR audio out Mux and Source Selection/DEV7_R_5: R348.1, U68.9, U110.8
/Audio Mux and Control/Headset LR audio out Mux and Source Selection/DEV7_R_6: R352.1, U70.9, U111.7
/Audio Mux and Control/Headset LR audio out Mux and Source Selection/DEV7_R_7: R356.1, U72.9, U111.8
/Audio Mux and Control/Headset LR audio out Mux and Source Selection/DEV_XBAR_C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: U57.1, U73.4
/Audio Mux and Control/Headset LR audio out Mux and Source Selection/DEV_XBAR_C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: U57.16, U73.5
/Audio Mux and Control/Headset LR audio out Mux and Source Selection/DEV_XBAR_C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: U57.15, U73.6
/Audio Mux and Control/Headset LR audio out Mux and Source Selection/DEV_XBAR_C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: U59.1, U73.7
/Audio Mux and Control/Headset LR audio out Mux and Source Selection/DEV_XBAR_C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: U59.16, U73.8
/Audio Mux and Control/Headset LR audio out Mux and Source Selection/DEV_XBAR_C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: U59.15, U73.9
/Audio Mux and Control/Headset LR audio out Mux and Source Selection/DEV_XBAR_C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: U61.1, U73.10
/Audio Mux and Control/Headset LR audio out Mux and Source Selection/DEV_XBAR_C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: U61.16, U73.11
/Audio Mux and Control/Headset LR audio out Mux and Source Selection/DEV_XBAR_C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: U61.15, U73.13
/Audio Mux and Control/Headset LR audio out Mux and Source Selection/DEV_XBAR_C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: U63.1, U73.14
/Audio Mux and Control/Headset LR audio out Mux and Source Selection/DEV_XBAR_C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: U63.16, U73.15
/Audio Mux and Control/Headset LR audio out Mux and Source Selection/DEV_XBAR_C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: U63.15, U73.16
/Audio Mux and Control/Headset LR audio out Mux and Source Selection/DEV_XBAR_C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: U65.1, U73.17
/Audio Mux and Control/Headset LR audio out Mux and Source Selection/DEV_XBAR_C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: U65.16, U73.18
/Audio Mux and Control/Headset LR audio out Mux and Source Selection/DEV_XBAR_C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: U65.15, U73.19
/Audio Mux and Control/Headset LR audio out Mux and Source Selection/DEV_XBAR_C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: U67.1, U73.20
/Audio Mux and Control/Headset LR audio out Mux and Source Selection/DEV_XBAR_C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: U67.16, U74.4
/Audio Mux and Control/Headset LR audio out Mux and Source Selection/DEV_XBAR_C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: U67.15, U74.5
/Audio Mux and Control/Headset LR audio out Mux and Source Selection/DEV_XBAR_C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: U69.1, U74.6
/Audio Mux and Control/Headset LR audio out Mux and Source Selection/DEV_XBAR_C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: U69.16, U74.7
/Audio Mux and Control/Headset LR audio out Mux and Source Selection/DEV_XBAR_C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: U69.15, U74.8
/Audio Mux and Control/Headset LR audio out Mux and Source Selection/DEV_XBAR_C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: U71.1, U74.9
/Audio Mux and Control/Headset LR audio out Mux and Source Selection/DEV_XBAR_C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: U71.16, U74.10
/Audio Mux and Control/Headset LR audio out Mux and Source Selection/DEV_XBAR_C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: U71.15, U74.11
/Audio Mux and Control/Headset LR audio out Mux and Source Selection/DEV_XBAR_C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: U58.1, U74.13
/Audio Mux and Control/Headset LR audio out Mux and Source Selection/DEV_XBAR_C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: U58.16, U74.14
/Audio Mux and Control/Headset LR audio out Mux and Source Selection/DEV_XBAR_C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: U58.15, U74.15
/Audio Mux and Control/Headset LR audio out Mux and Source Selection/DEV_XBAR_C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: U60.1, U74.16
/Audio Mux and Control/Headset LR audio out Mux and Source Selection/DEV_XBAR_C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: U60.16, U74.17
/Audio Mux and Control/Headset LR audio out Mux and Source Selection/DEV_XBAR_C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: U60.15, U74.18
/Audio Mux and Control/Headset LR audio out Mux and Source Selection/DEV_XBAR_C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: U62.1, U74.19
/Audio Mux and Control/Headset LR audio out Mux and Source Selection/DEV_XBAR_C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: U62.16, U74.20
/Audio Mux and Control/Headset LR audio out Mux and Source Selection/DEV_XBAR_C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: U62.15, U76.4
/Audio Mux and Control/Headset LR audio out Mux and Source Selection/DEV_XBAR_C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: U64.1, U76.5
/Audio Mux and Control/Headset LR audio out Mux and Source Selection/DEV_XBAR_C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: U64.16, U76.6
/Audio Mux and Control/Headset LR audio out Mux and Source Selection/DEV_XBAR_C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: U64.15, U76.7
/Audio Mux and Control/Headset LR audio out Mux and Source Selection/DEV_XBAR_C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: U66.1, U76.8
/Audio Mux and Control/Headset LR audio out Mux and Source Selection/DEV_XBAR_C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: U66.16, U76.9
/Audio Mux and Control/Headset LR audio out Mux and Source Selection/DEV_XBAR_C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: U66.15, U76.10
/Audio Mux and Control/Headset LR audio out Mux and Source Selection/DEV_XBAR_C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: U68.1, U76.11
/Audio Mux and Control/Headset LR audio out Mux and Source Selection/DEV_XBAR_C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: U68.16, U76.13
/Audio Mux and Control/Headset LR audio out Mux and Source Selection/DEV_XBAR_C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: U68.15, U76.14
/Audio Mux and Control/Headset LR audio out Mux and Source Selection/DEV_XBAR_C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: U70.1, U76.15
/Audio Mux and Control/Headset LR audio out Mux and Source Selection/DEV_XBAR_C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: U70.16, U76.16
/Audio Mux and Control/Headset LR audio out Mux and Source Selection/DEV_XBAR_C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: U70.15, U76.17
/Audio Mux and Control/Headset LR audio out Mux and Source Selection/DEV_XBAR_C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: U72.1, U76.18
/Audio Mux and Control/Headset LR audio out Mux and Source Selection/DEV_XBAR_C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: U72.16, U76.19
/Audio Mux and Control/Headset LR audio out Mux and Source Selection/DEV_XBAR_C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: U72.15, U76.20
/Audio Mux and Control/Headset LR audio out Mux and Source Selection/Dev 0 1:8 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: R107.2, R108.1, R114.2, R119.2, R123.2, R127.2, R131.2, R135.2, R139.2, U78.1
/Audio Mux and Control/Headset LR audio out Mux and Source Selection/Dev 0 1:8 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: R111.2, R113.1, R117.2, R121.2, R125.2, R129.2, R133.2, R137.2, R141.2, U78.7
/Audio Mux and Control/Headset LR audio out Mux and Source Selection/Dev 1 1:8 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: R143.2, R144.1, R150.2, R155.2, R159.2, R163.2, R167.2, R171.2, R175.2, U83.1
/Audio Mux and Control/Headset LR audio out Mux and Source Selection/Dev 1 1:8 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: R147.2, R149.1, R153.2, R157.2, R161.2, R165.2, R169.2, R173.2, R177.2, U83.7
/Audio Mux and Control/Headset LR audio out Mux and Source Selection/Dev 2 1:8 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: R179.2, R180.1, R186.2, R191.2, R195.2, R199.2, R203.2, R207.2, R211.2, U88.1
/Audio Mux and Control/Headset LR audio out Mux and Source Selection/Dev 2 1:8 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: R183.2, R185.1, R189.2, R193.2, R197.2, R201.2, R205.2, R209.2, R213.2, U88.7
/Audio Mux and Control/Headset LR audio out Mux and Source Selection/Dev 3 1:8 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: R215.2, R216.1, R222.2, R227.2, R231.2, R235.2, R239.2, R243.2, R247.2, U93.1
/Audio Mux and Control/Headset LR audio out Mux and Source Selection/Dev 3 1:8 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: R219.2, R221.1, R225.2, R229.2, R233.2, R237.2, R241.2, R245.2, R249.2, U93.7
/Audio Mux and Control/Headset LR audio out Mux and Source Selection/Dev 4 1:8 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: R359.2, R360.1, R366.2, R371.2, R375.2, R379.2, R383.2, R387.2, R391.2, U113.1
/Audio Mux and Control/Headset LR audio out Mux and Source Selection/Dev 4 1:8 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: R363.2, R365.1, R369.2, R373.2, R377.2, R381.2, R385.2, R389.2, R393.2, U113.7
/Audio Mux and Control/Headset LR audio out Mux and Source Selection/Dev 5 1:8 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: R251.2, R252.1, R258.2, R263.2, R267.2, R271.2, R275.2, R279.2, R283.2, U98.1
/Audio Mux and Control/Headset LR audio out Mux and Source Selection/Dev 5 1:8 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: R255.2, R257.1, R261.2, R265.2, R269.2, R273.2, R277.2, R281.2, R285.2, U98.7
/Audio Mux and Control/Headset LR audio out Mux and Source Selection/Dev 6 1:8 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: R287.2, R288.1, R294.2, R299.2, R303.2, R307.2, R311.2, R315.2, R319.2, U103.1
/Audio Mux and Control/Headset LR audio out Mux and Source Selection/Dev 6 1:8 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: R291.2, R293.1, R297.2, R301.2, R305.2, R309.2, R313.2, R317.2, R321.2, U103.7
/Audio Mux and Control/Headset LR audio out Mux and Source Selection/Dev 7 1:8 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: R323.2, R324.1, R330.2, R335.2, R339.2, R343.2, R347.2, R351.2, R355.2, U108.1
/Audio Mux and Control/Headset LR audio out Mux and Source Selection/Dev 7 1:8 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: R327.2, R329.1, R333.2, R337.2, R341.2, R345.2, R349.2, R353.2, R357.2, U108.7
/Audio Mux and Control/Headset LR audio out Mux and Source Selection/MIDL0: U11.2, U57.8
/Audio Mux and Control/Headset LR audio out Mux and Source Selection/MIDL1: U11.12, U59.8
/Audio Mux and Control/Headset LR audio out Mux and Source Selection/MIDL2: U13.2, U61.8
/Audio Mux and Control/Headset LR audio out Mux and Source Selection/MIDL3: U13.12, U63.8
/Audio Mux and Control/Headset LR audio out Mux and Source Selection/MIDL4: U14.2, U65.8
/Audio Mux and Control/Headset LR audio out Mux and Source Selection/MIDL5: U14.12, U67.8
/Audio Mux and Control/Headset LR audio out Mux and Source Selection/MIDL6: U16.2, U69.8
/Audio Mux and Control/Headset LR audio out Mux and Source Selection/MIDL7: U16.12, U71.8
/Audio Mux and Control/Headset LR audio out Mux and Source Selection/MIDR0: U11.9, U58.8
/Audio Mux and Control/Headset LR audio out Mux and Source Selection/MIDR1: U11.19, U60.8
/Audio Mux and Control/Headset LR audio out Mux and Source Selection/MIDR2: U13.9, U62.8
/Audio Mux and Control/Headset LR audio out Mux and Source Selection/MIDR3: U13.19, U64.8
/Audio Mux and Control/Headset LR audio out Mux and Source Selection/MIDR4: U14.9, U66.8
/Audio Mux and Control/Headset LR audio out Mux and Source Selection/MIDR5: U14.19, U68.8
/Audio Mux and Control/Headset LR audio out Mux and Source Selection/MIDR6: U16.9, U70.8
/Audio Mux and Control/Headset LR audio out Mux and Source Selection/MIDR7: U16.19, U72.8
/Audio Mux and Control/Headset LR audio out Mux and Source Selection/MIXER_L_IN: J5.1, R398.2
/Audio Mux and Control/Headset LR audio out Mux and Source Selection/MIXER_OUT_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: R394.1, U11.4, U117.1
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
